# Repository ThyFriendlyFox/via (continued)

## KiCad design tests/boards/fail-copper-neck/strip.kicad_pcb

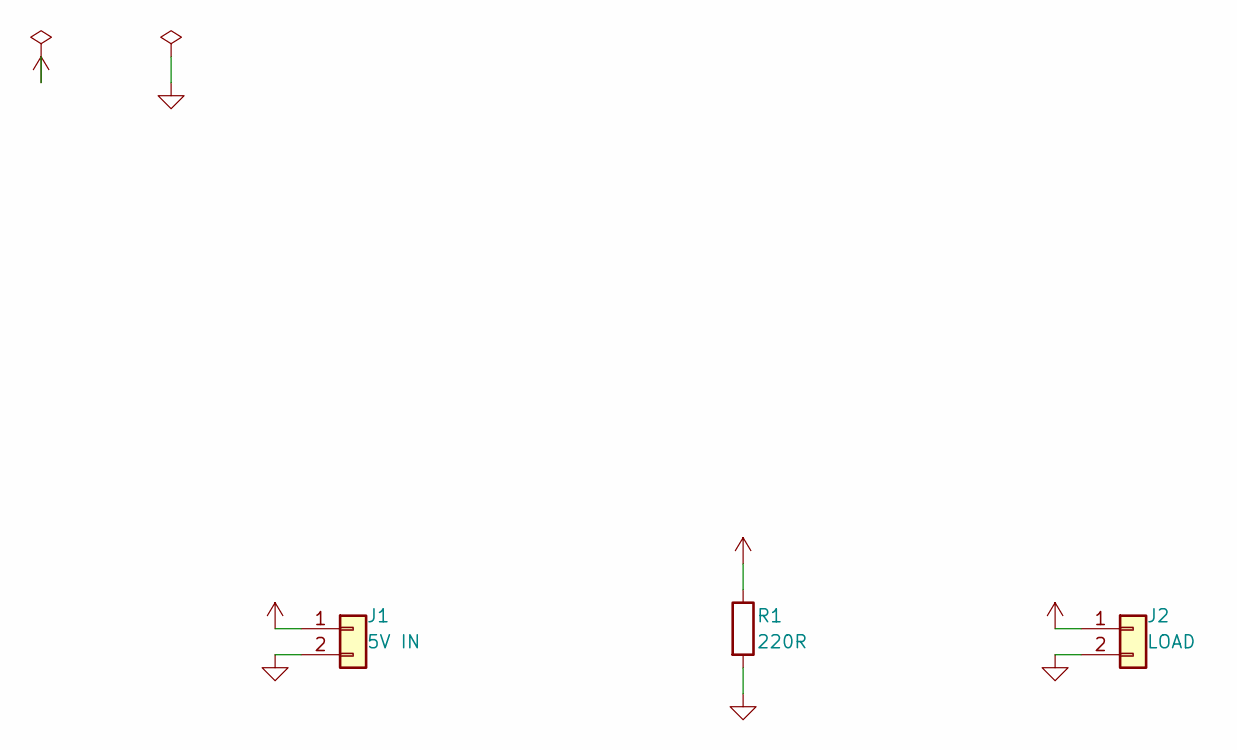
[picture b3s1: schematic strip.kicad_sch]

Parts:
J1: 5V IN; PinHeader_1x02_P2.54mm_Vertical
J2: LOAD; PinHeader_1x02_P2.54mm_Vertical
R1: 220R; R_2512_6332Metric

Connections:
+5V: J1.1, J2.1, R1.1
GND: J1.2, J2.2, R1.2

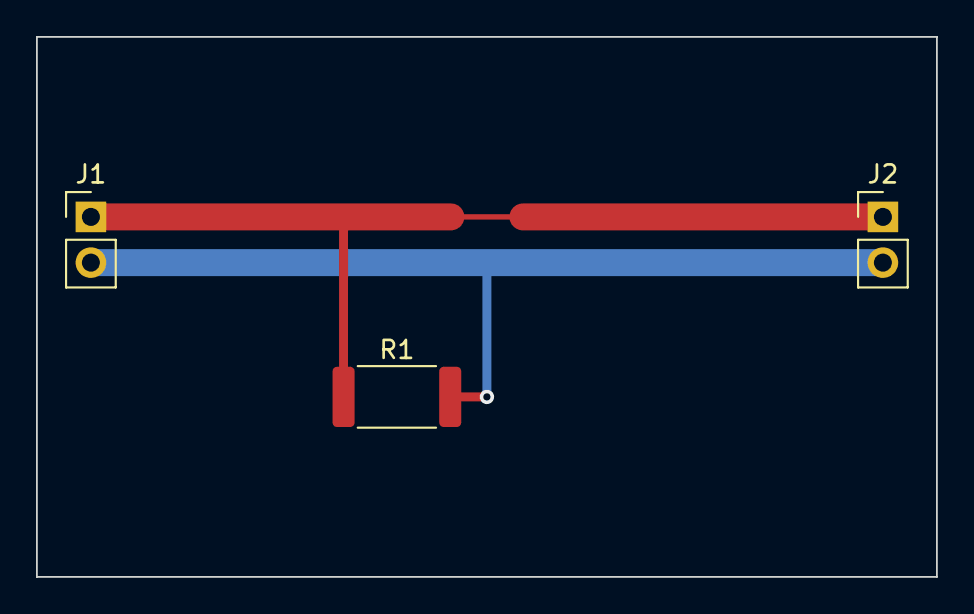
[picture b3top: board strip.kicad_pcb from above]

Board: 2 copper layers, 50.0 x 30.0 mm, 3 parts (0 on the bottom side), 2 nets.

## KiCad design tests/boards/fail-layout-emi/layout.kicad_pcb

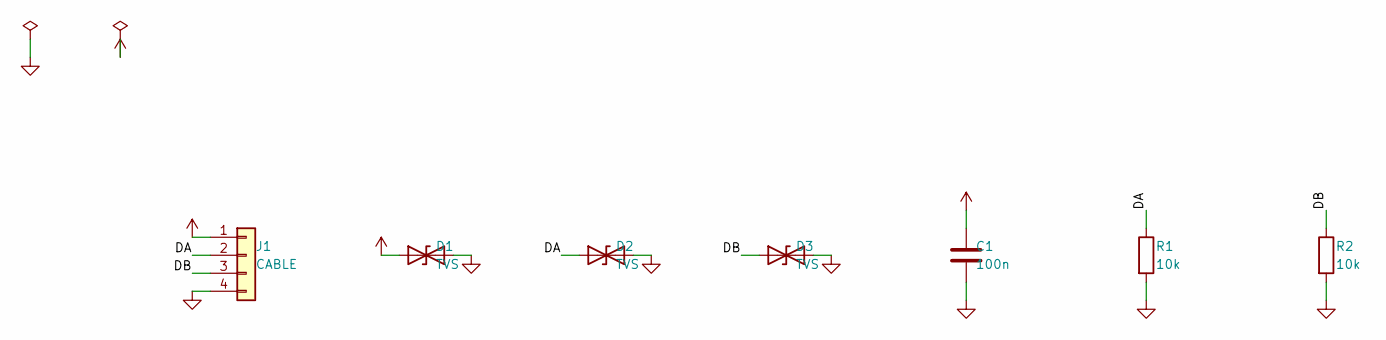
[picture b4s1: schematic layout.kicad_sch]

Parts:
C1: 100n; C_0805_2012Metric
D1, D2, D3: TVS; D_SOD-323
J1: CABLE; PinHeader_1x04_P2.54mm_Vertical
R1, R2: 10k; R_0805_2012Metric

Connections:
/DA: D2.1 (A1), J1.2, R1.1
/DB: D3.1 (A1), J1.3, R2.1
GND: C1.2, D1.2 (A2), D2.2 (A2), D3.2 (A2), J1.4, R1.2, R2.2
VBUS: C1.1, D1.1 (A1), J1.1

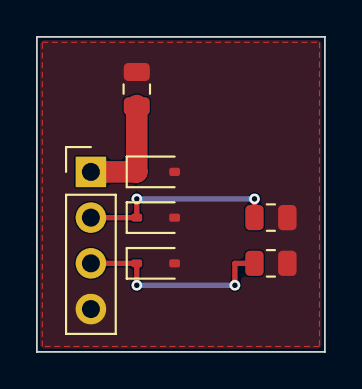
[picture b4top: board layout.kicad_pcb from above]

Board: 2 copper layers, 16.0 x 17.5 mm, 7 parts (0 on the bottom side), 4 nets.
